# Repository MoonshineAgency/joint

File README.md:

# Joint

Project of the MQTT controller based on the ESP32 for horticulture applications.
Contains firmware and KiCad projects for controllers.

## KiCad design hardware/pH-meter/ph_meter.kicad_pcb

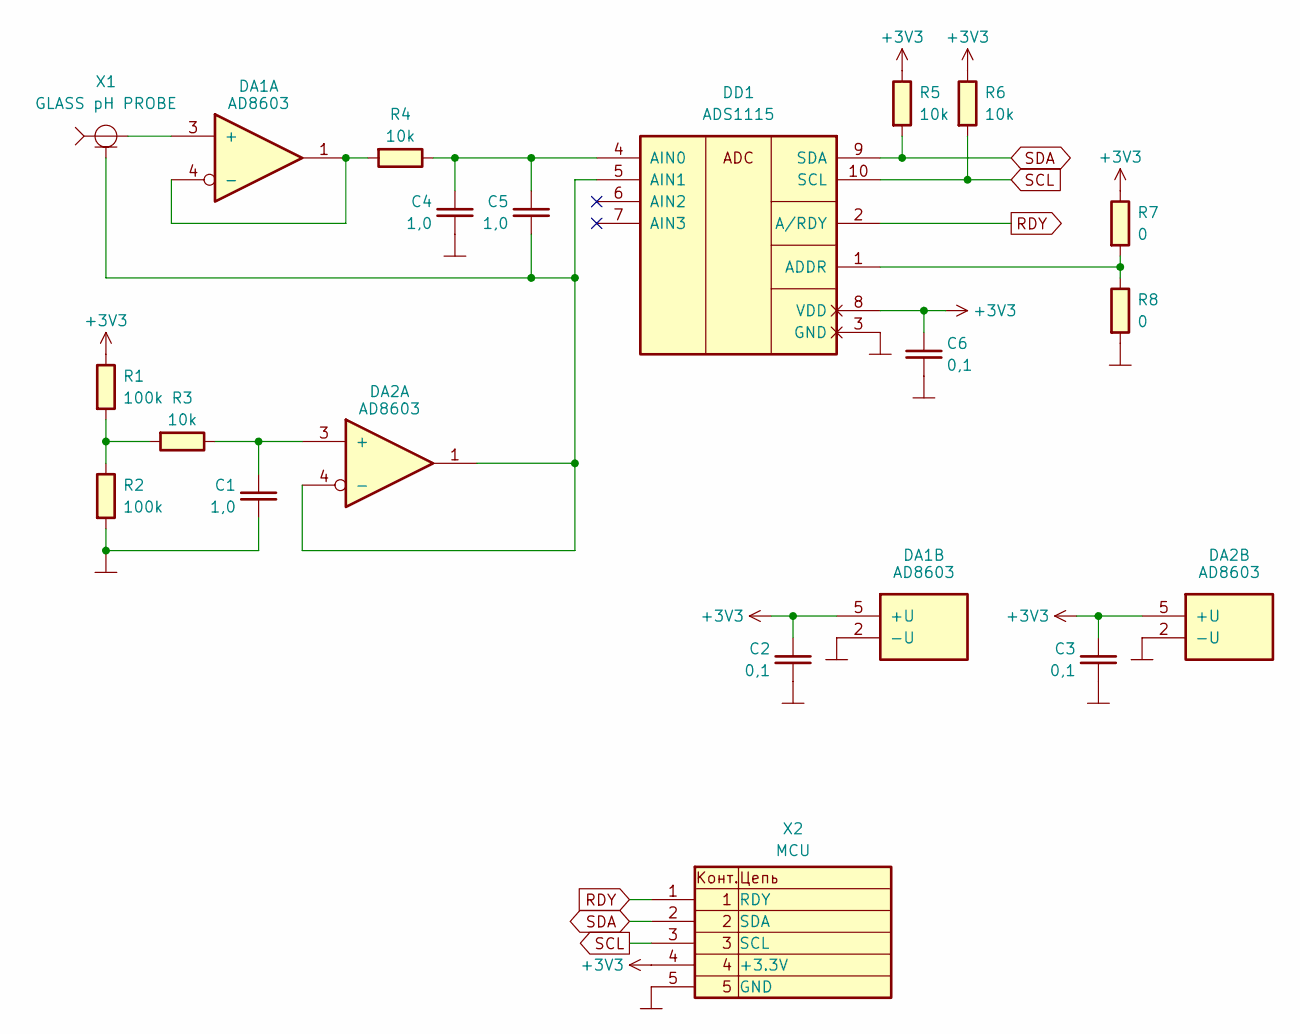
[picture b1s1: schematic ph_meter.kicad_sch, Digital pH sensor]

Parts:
C1, C4, C5: 1,0; C_0805_2012Metric_Pad1.18x1.45mm_HandSolder
C2, C3, C6: 0,1; C_0805_2012Metric_Pad1.18x1.45mm_HandSolder
DA1, DA2: AD8603; TSOT-23-5_HandSoldering
DD1: ADS1115; MSOP-10_3x3mm_P0.5mm
R1, R2: 100k; R_0805_2012Metric_Pad1.20x1.40mm_HandSolder
R3, R4, R5, R6: 10k; R_0805_2012Metric_Pad1.20x1.40mm_HandSolder
R7, R8: 0; R_0805_2012Metric_Pad1.20x1.40mm_HandSolder
X1: GLASS pH PROBE; BNC_Amphenol_B6252HB-NPP3G-50_Horizontal
X2: MCU; PinHeader_1x05_P2.54mm_Vertical

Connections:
+3V3: C2.2, C3.2, C6.2, DA1.5 (+U), DA2.5 (+U), DD1.8 (VDD), R1.2 (R), R5.2 (R), R6.2 (R), R7.2 (R), X2.4
GND: C1.1, C2.1, C3.1, C4.1, C6.1, DA1.2 (-U), DA2.2 (-U), DD1.3 (GND), R2.1 (L), R8.1 (L), X2.5
unnamed: DA1.3 (+), X1.1
unnamed: DA1.1, DA1.4 (-), R4.1 (L)
unnamed: C1.2, DA2.3 (+), R3.2 (R)
unnamed: C5.1, DA2.1, DA2.4 (-), DD1.5 (AIN1), X1.2
unnamed: DD1.1 (ADDR), R7.1 (L), R8.2 (R)
unnamed: C4.2, C5.2, DD1.4 (AIN0), R4.2 (R)
unnamed: R1.1 (L), R2.2 (R), R3.1 (L)
RDY: DD1.2 (A/RDY), X2.1
SCL: DD1.10 (SCL), R6.1 (L), X2.3
SDA: DD1.9 (SDA), R5.1 (L), X2.2

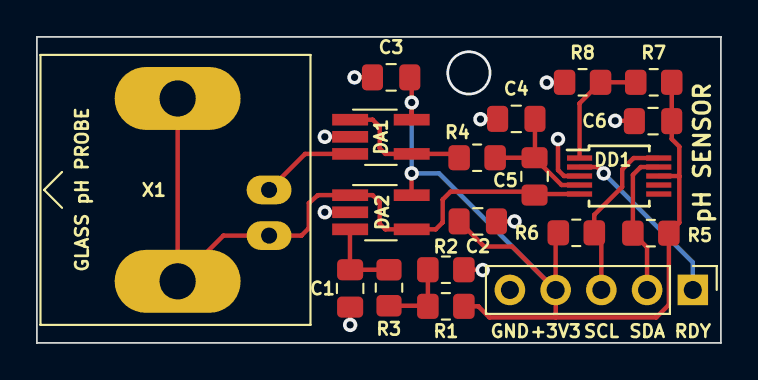
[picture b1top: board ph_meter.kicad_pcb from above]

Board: 2 copper layers, 38.0 x 17.0 mm, 19 parts (0 on the bottom side), 12 nets.

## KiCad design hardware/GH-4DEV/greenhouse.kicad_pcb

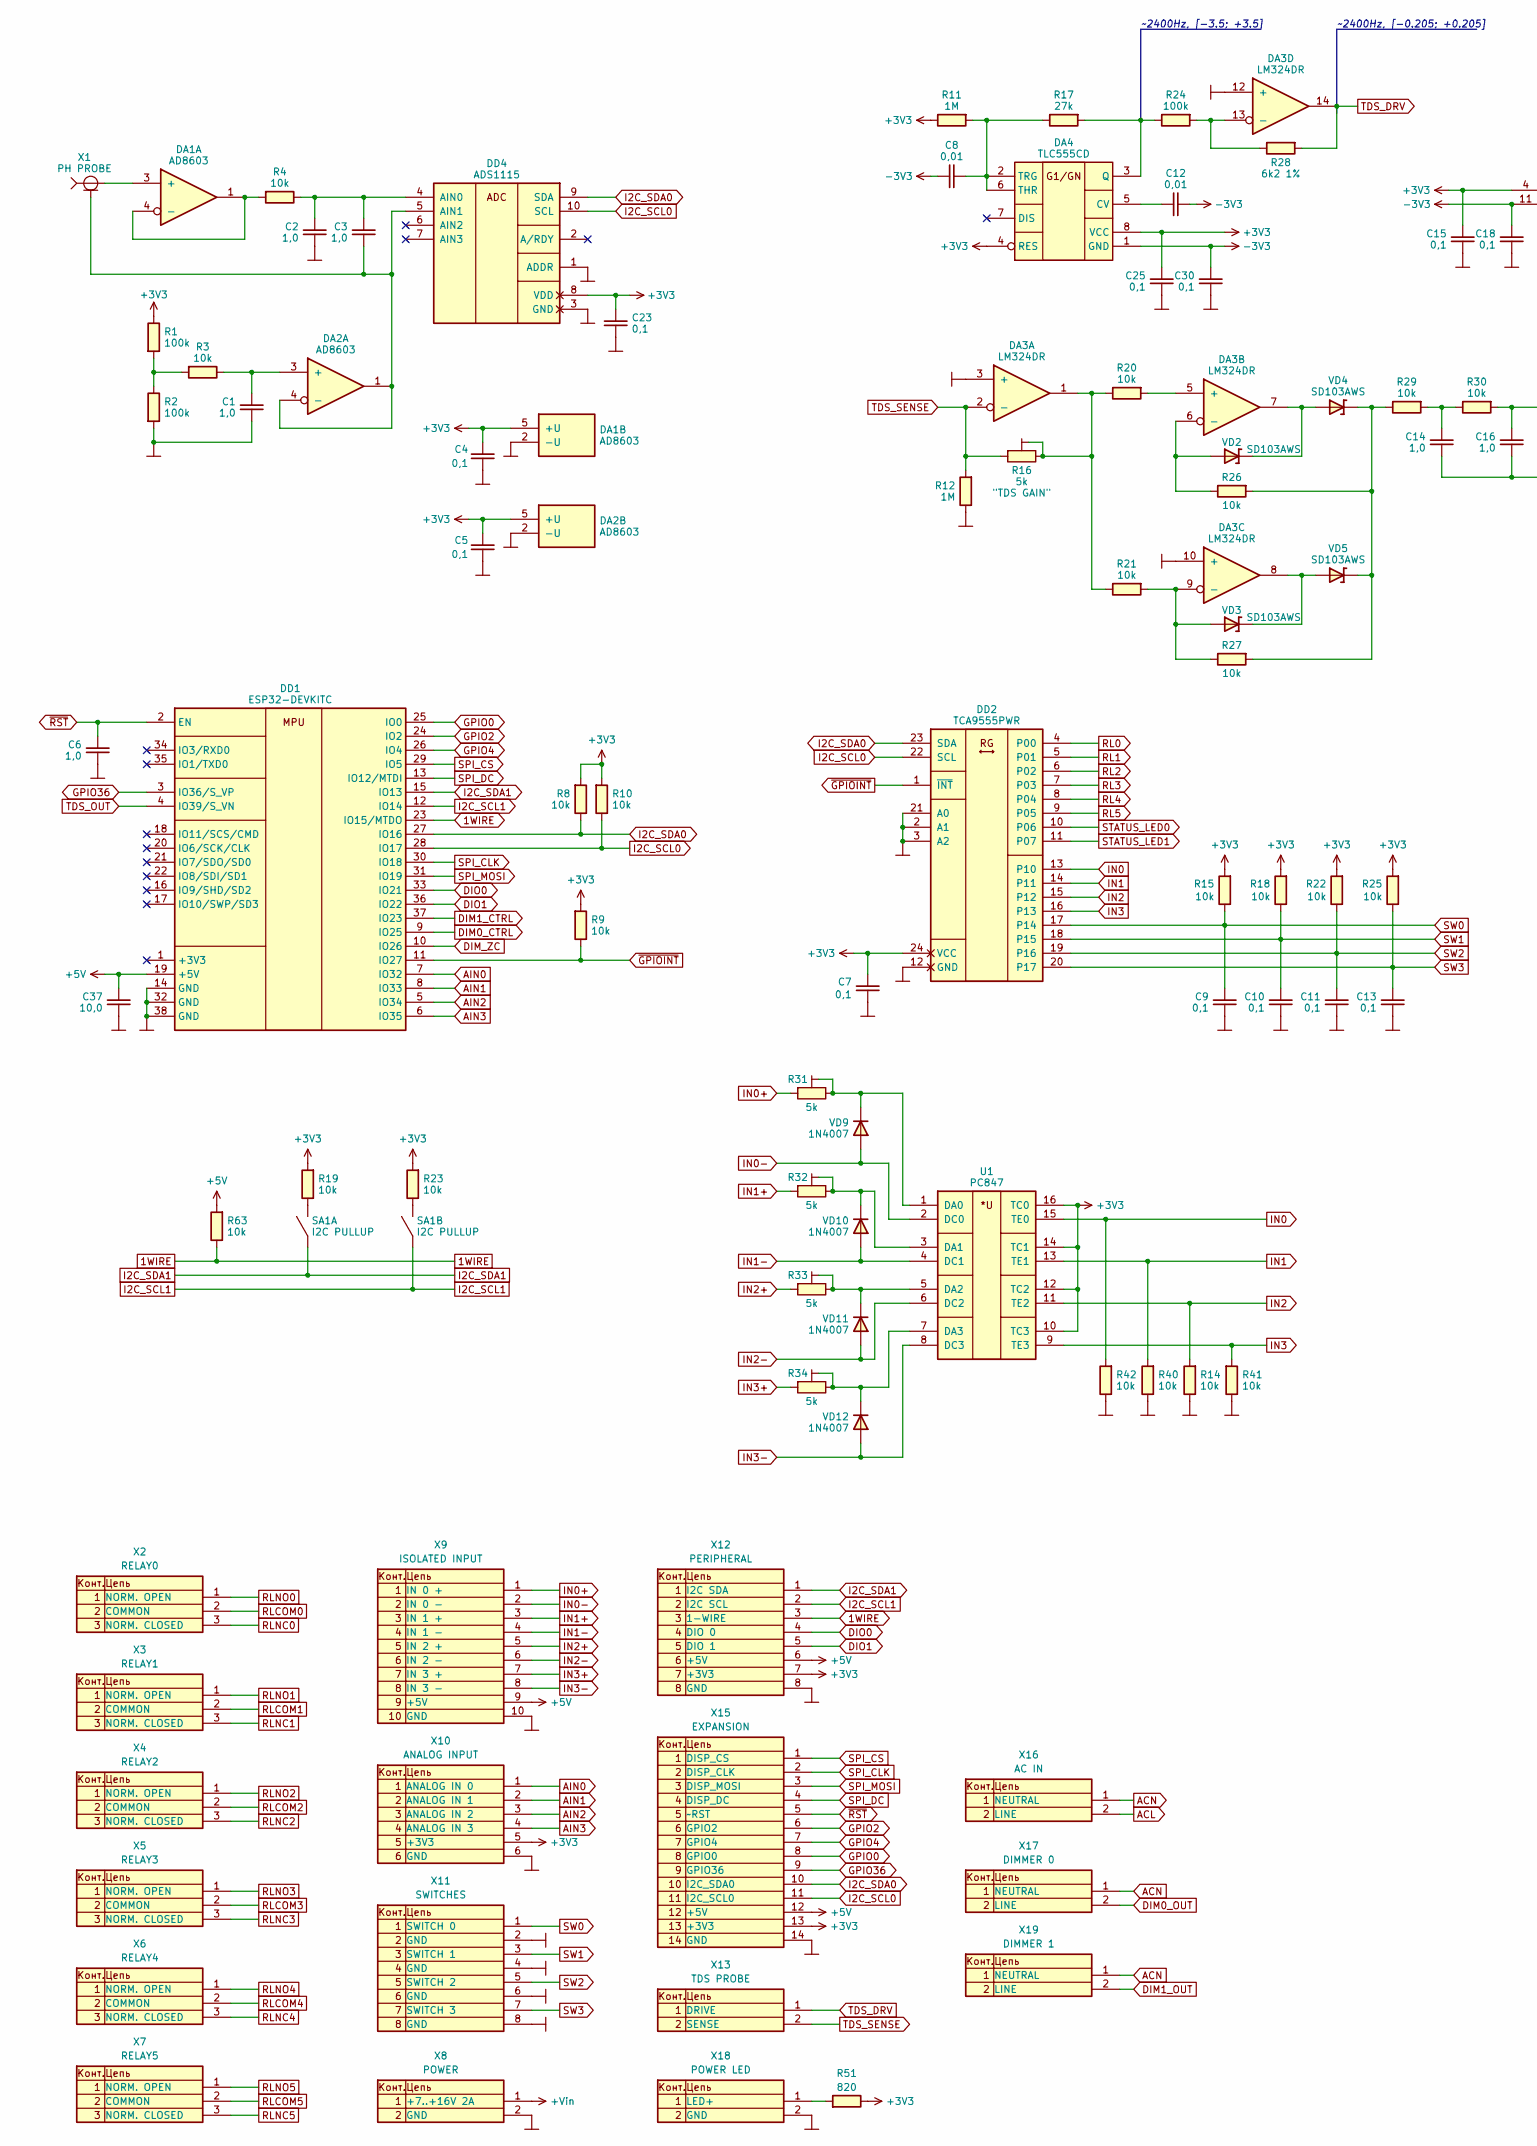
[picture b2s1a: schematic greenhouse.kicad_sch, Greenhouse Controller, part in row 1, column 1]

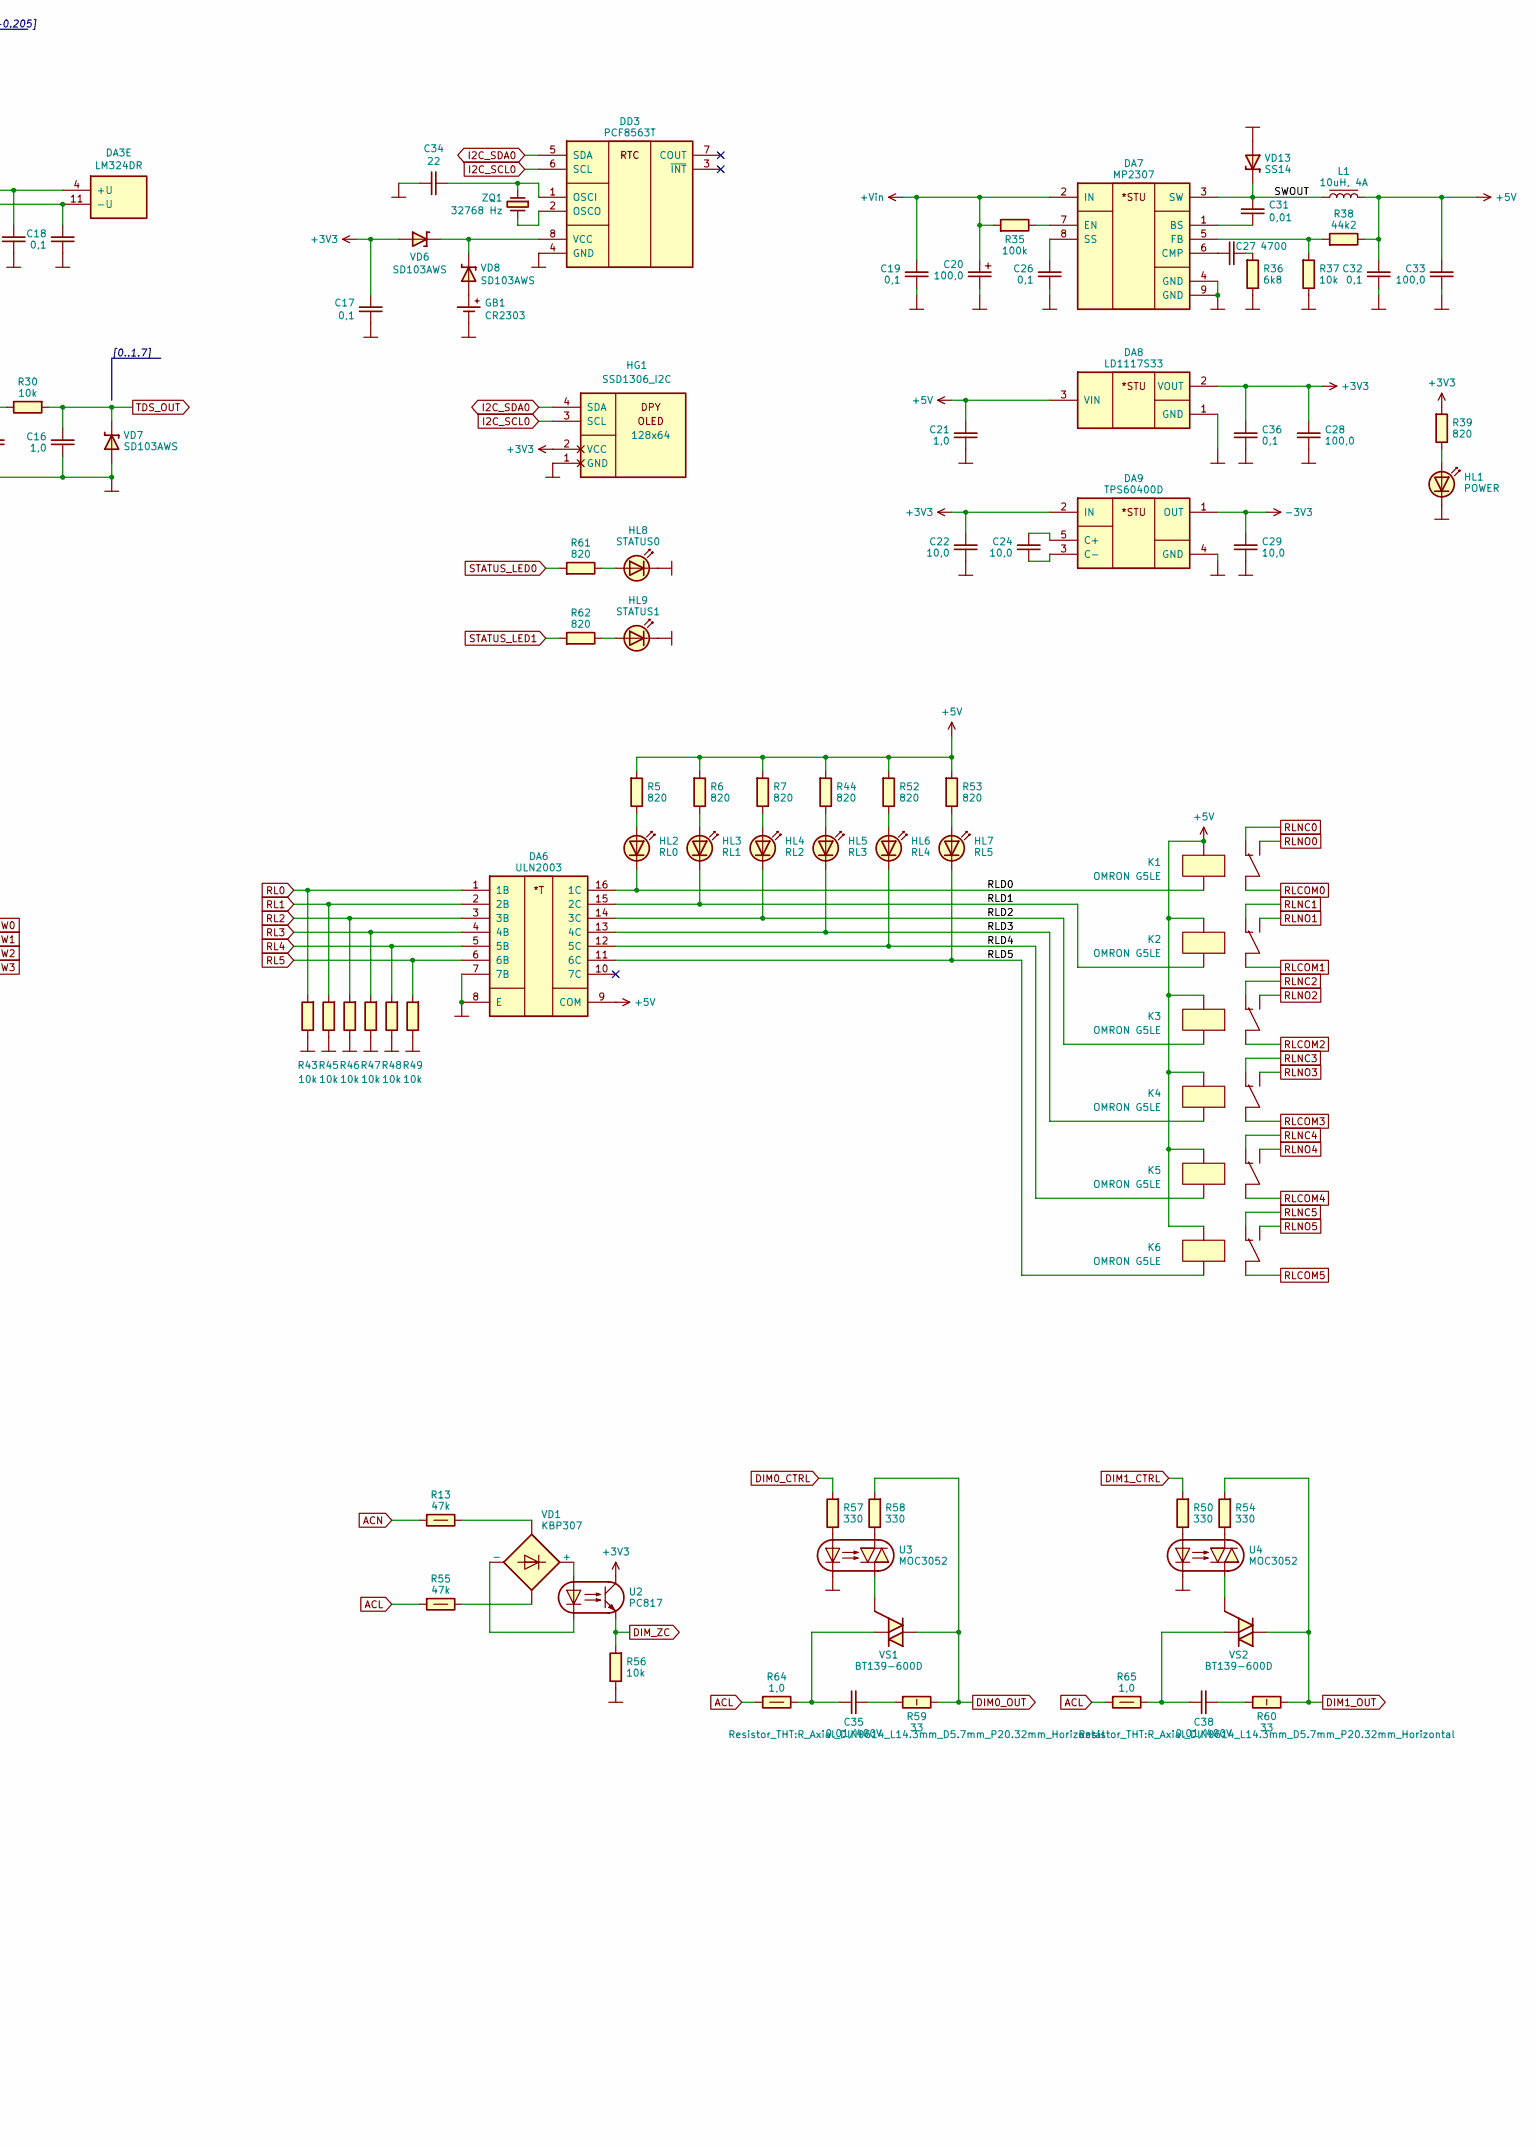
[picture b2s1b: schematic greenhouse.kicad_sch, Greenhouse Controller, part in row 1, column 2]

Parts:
C1, C2, C3, C6, C14, C16, C21: 1,0; C_0805_2012Metric_Pad1.18x1.45mm_HandSolder
C4, C5, C7, C9, C10, C11, C13, C15, C17, C18, C19, C23, C25, C26, C30, C32, C36: 0,1; C_0805_2012Metric_Pad1.18x1.45mm_HandSolder
C8, C12, C31: 0,01; C_0805_2012Metric_Pad1.18x1.45mm_HandSolder
C20: 100,0; CP_EIA-7343-31_Kemet-D_Pad2.25x2.55mm_HandSolder
C22, C24, C29, C37: 10,0; C_0805_2012Metric_Pad1.18x1.45mm_HandSolder
C27: 4700; C_0805_2012Metric_Pad1.18x1.45mm_HandSolder
C28, C33: 100,0; C_1210_3225Metric_Pad1.33x2.70mm_HandSolder
C34: 22; C_0805_2012Metric_Pad1.18x1.45mm_HandSolder
C35, C38: 0,01/400V; C_Rect_L13.0mm_W5.0mm_P10.00mm_FKS3_FKP3_MKS4
DA1, DA2: AD8603; TSOT-23-5_HandSoldering
DA3: LM324DR; SOIC-14_3.9x8.7mm_P1.27mm
DA4: TLC555CD; SOIC-8_3.9x4.9mm_P1.27mm
DA6: ULN2003; SOIC-16_3.9x9.9mm_P1.27mm
DA7: MP2307; HSOP-8-1EP_3.9x4.9mm_P1.27mm_EP2.41x3.1mm_ThermalVias
DA8: LD1117S33; SOT-223-3_TabPin2
DA9: TPS60400D; SOT-23-5_HandSoldering
DD1: ESP32-DEVKITC
DD2: TCA9555PWR; TSSOP-24_4.4x7.8mm_P0.65mm
DD3: PCF8563T; SOIC-8_3.9x4.9mm_P1.27mm
DD4: ADS1115; MSOP-10_3x3mm_P0.5mm
GB1: CR2303; BAT_BS-7
HG1: SSD1306_I2C; SSD1306_0.96_Oled
HL1: POWER; LED_0805_2012Metric_Pad1.15x1.40mm_HandSolder
HL2: RL0; LED_0805_2012Metric_Pad1.15x1.40mm_HandSolder
HL3: RL1; LED_0805_2012Metric_Pad1.15x1.40mm_HandSolder
HL4: RL2; LED_0805_2012Metric_Pad1.15x1.40mm_HandSolder
HL5: RL3; LED_0805_2012Metric_Pad1.15x1.40mm_HandSolder
HL6: RL4; LED_0805_2012Metric_Pad1.15x1.40mm_HandSolder
HL7: RL5; LED_0805_2012Metric_Pad1.15x1.40mm_HandSolder
HL8: STATUS0; LED_0805_2012Metric_Pad1.15x1.40mm_HandSolder
HL9: STATUS1; LED_0805_2012Metric_Pad1.15x1.40mm_HandSolder
K1, K2, K3, K4, K5, K6: OMRON G5LE; Relay_SPDT_Omron-G5LE-1
L1: 10uH, 4A; L_0808
R1, R2, R24, R35: 100k; R_0805_2012Metric_Pad1.20x1.40mm_HandSolder
R3, R4, R8, R9, R10, R14, R15, R18, R19, R20, R21, R22, R23, R25, R26, R27, R29, R30, R37, R40, R41, R42, R43, R45, R46, R47, R48, R49, R56, R63: 10k; R_0805_2012Metric_Pad1.20x1.40mm_HandSolder
R5, R6, R7, R39, R44, R51, R52, R53, R61, R62: 820; R_0805_2012Metric_Pad1.20x1.40mm_HandSolder
R11, R12: 1M; R_0805_2012Metric_Pad1.20x1.40mm_HandSolder
R13, R55: 47k; R_Axial_DIN0309_L9.0mm_D3.2mm_P12.70mm_Horizontal
R16, R31, R32, R33, R34: 5k; Potentiometer_Bourns_3296W_Vertical
R17: 27k; R_0805_2012Metric_Pad1.20x1.40mm_HandSolder
R28: 6k2 1%; R_0805_2012Metric_Pad1.20x1.40mm_HandSolder
R36: 6k8; R_0805_2012Metric_Pad1.20x1.40mm_HandSolder
R38: 44k2; R_0805_2012Metric_Pad1.20x1.40mm_HandSolder
R50, R54, R57, R58: 330; R_0805_2012Metric_Pad1.20x1.40mm_HandSolder
R59, R60: 33; R_Axial_DIN0614_L14.3mm_D5.7mm_P20.32mm_Horizontal
R64, R65: 1,0; R_Axial_DIN0309_L9.0mm_D3.2mm_P2.54mm_Vertical
SA1: I2C PULLUP; SW_DIP_SPSTx02_Slide_6.7x6.64mm_W7.62mm_P2.54mm_LowProfile
U1: PC847; DIP-16_W7.62mm_LongPads
U2: PC817; DIP-4_W7.62mm_LongPads
U3, U4: MOC3052; DIP-6_W7.62mm_LongPads
VD1: KBP307; Diode_Bridge_Vishay_KBPM
VD2, VD3, VD4, VD5, VD6, VD7, VD8: SD103AWS; D_SOD-323_HandSoldering
VD9, VD10, VD11, VD12: 1N4007; D_SOD-123
VD13: SS14; D_SMA
VS1, VS2: BT139-600D; TO-220-3_Vertical
X1: PH PROBE; BNC_Amphenol_B6252HB-NPP3G-50_Horizontal
X2: RELAY0; TerminalBlock_bornier-3_P5.08mm
X3: RELAY1; TerminalBlock_bornier-3_P5.08mm
X4: RELAY2; TerminalBlock_bornier-3_P5.08mm
X5: RELAY3; TerminalBlock_bornier-3_P5.08mm
X6: RELAY4; TerminalBlock_bornier-3_P5.08mm
X7: RELAY5; TerminalBlock_bornier-3_P5.08mm
X8: POWER; TerminalBlock_bornier-2_P5.08mm
X9: ISOLATED INPUT; TerminalBlock_bornier-10_P5.08mm
X10: ANALOG INPUT; TerminalBlock_bornier-6_P5.08mm
X11: SWITCHES; TerminalBlock_bornier-8_P5.08mm
X12: PERIPHERAL; TerminalBlock_bornier-8_P5.08mm
X13: TDS PROBE; TerminalBlock_bornier-2_P5.08mm
X15: EXPANSION; PinHeader_2x07_P2.54mm_Vertical
X16: AC IN; TerminalBlock_bornier-2_P5.08mm
X17: DIMMER 0; TerminalBlock_bornier-2_P5.08mm
X18: POWER LED; PinHeader_1x02_P2.54mm_Vertical
X19: DIMMER 1; TerminalBlock_bornier-2_P5.08mm
ZQ1: 32768 Hz; Crystal_DS26_D2.0mm_L6.0mm_Horizontal

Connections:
1WIRE: DD1.23 (IO15/MTDO), R63.2 (R), X12.3
+3V3: C4.1, C5.1, C7.1, C15.1, C17.1, C22.1, C23.2, C25.1, C28.1, C36.1, DA1.5 (+U), DA2.5 (+U), DA3.4 (+U), DA4.4 (RES), DA4.8 (VCC), DA8.2 (VOUT), DA9.2 (IN), DD2.24 (VCC), DD4.8 (VDD), HG1.2 (VCC), R1.2 (R), R8.1 (L), R9.1 (L), R10.1 (L), R11.2 (R), R15.1 (L), R18.1 (L), R19.1 (L), R22.1 (L), R23.1 (L), R25.1 (L), R39.1 (L), R51.2 (R), U1.10 (TC3), U1.12 (TC2), U1.14 (TC1), U1.16 (TC0), U2.4, VD6.2 (A), X10.5, X12.7, X15.13
+5V: C21.1, C32.1, C33.1, C37.1, DA6.9 (COM), DA8.3 (VIN), DD1.19 (+5V), K1.2, K2.2, K3.2, K4.2, K5.2, K6.2, L1.2, R5.1 (L), R6.1 (L), R7.1 (L), R38.2 (R), R44.1 (L), R52.1 (L), R53.1 (L), R63.1 (L), X9.9, X12.6, X15.12
+Vin: C19.1, C20.1, DA7.2 (IN), R35.1 (L), X8.1
-3V3: C8.2, C12.1, C18.1, C29.1, C30.1, DA3.11 (-U), DA4.1 (GND), DA9.1 (OUT)
/RLD0: DA6.16 (1C), HL2.1 (K), K1.5
/RLD1: DA6.15 (2C), HL3.1 (K), K2.5
/RLD2: DA6.14 (3C), HL4.1 (K), K3.5
/RLD3: DA6.13 (4C), HL5.1 (K), K4.5
/RLD4: DA6.12 (5C), HL6.1 (K), K5.5
/RLD5: DA6.11 (6C), HL7.1 (K), K6.5
/SWOUT: C31.1, DA7.3 (SW), L1.1, VD13.1 (K)
ACL: R55.1 (L), R64.1 (L), R65.1 (L), X16.2
ACN: R13.1 (L), X16.1, X17.1, X19.1
AIN0: DD1.7 (IO32), X10.1
AIN1: DD1.8 (IO33), X10.2
AIN2: DD1.5 (IO34), X10.3
AIN3: DD1.6 (IO35), X10.4
DIM0_CTRL: DD1.9 (IO25), R57.1 (L)
DIM0_OUT: R58.1 (L), R59.2 (R), VS1.2 (A), X17.2
DIM1_CTRL: DD1.37 (IO23), R50.1 (L)
DIM1_OUT: R54.1 (L), R60.2 (R), VS2.2 (A), X19.2
DIM_ZC: DD1.10 (IO26), R56.1 (L), U2.3
DIO0: DD1.33 (IO21), X12.4
DIO1: DD1.36 (IO22), X12.5
GND: C1.1, C2.1, C4.2, C5.2, C6.2, C7.2, C9.2, C10.2, C11.2, C13.2, C14.2, C15.2, C16.2, C17.2, C18.2, C19.2, C20.2, C21.2, C22.2, C23.1, C25.2, C26.2, C28.2, C29.2, C30.2, C32.2, C33.2, C34.2, C36.2, C37.2, DA1.2 (-U), DA2.2 (-U), DA3.3 (+), DA3.10 (+), DA3.12 (+), DA6.7 (7B), DA6.8 (E), DA7.4 (GND), DA7.9 (GND), DA8.1 (GND), DA9.4 (GND), DD1.14 (GND), DD1.32 (GND), DD1.38 (GND), DD2.2 (A1), DD2.3 (A2), DD2.12 (GND), DD2.21 (A0), DD3.4 (GND), DD4.1 (ADDR), DD4.3 (GND), GB1.2, HG1.1 (GND), HL1.1 (K), HL8.1 (K), HL9.1 (K), R2.1 (L), R12.2 (R), R14.2 (R), R36.2 (R), R37.2 (R), R40.2 (R), R41.2 (R), R42.2 (R), R43.2 (R), R45.2 (R), R46.2 (R), R47.2 (R), R48.2 (R), R49.2 (R), R56.2 (R), U3.2, U4.2, VD7.2 (A), VD13.2 (A), X8.2, X9.10, X10.6, X11.2, X11.4, X11.6, X11.8, X12.8, X15.14, X18.2
GPIO0: DD1.25 (IO0), X15.8
GPIO2: DD1.24 (IO2), X15.6
GPIO4: DD1.26 (IO4), X15.7
GPIO36: DD1.3 (IO36/S_VP), X15.9
I2C_SCL0: DD1.28 (IO17), DD2.22 (SCL), DD3.6 (SCL), DD4.10 (SCL), HG1.3 (SCL), R10.2 (R), X15.11
I2C_SCL1: DD1.12 (IO14), SA1.2 (L), X12.2
I2C_SDA0: DD1.27 (IO16), DD2.23 (SDA), DD3.5 (SDA), DD4.9 (SDA), HG1.4 (SDA), R8.2 (R), X15.10
I2C_SDA1: DD1.15 (IO13), SA1.1 (L), X12.1
IN0: DD2.13 (P10), R42.1 (L), U1.15 (TE0)
IN0+: R31.1, X9.1
IN0-: U1.2 (DC0), VD9.2 (A), X9.2
IN1: DD2.14 (P11), R40.1 (L), U1.13 (TE1)
IN1+: R32.1, X9.3
IN1-: U1.4 (DC1), VD10.2 (A), X9.4
IN2: DD2.15 (P12), R14.1 (L), U1.11 (TE2)
IN2+: R33.1, X9.5
IN2-: U1.6 (DC2), VD11.2 (A), X9.6
IN3: DD2.16 (P13), R41.1 (L), U1.9 (TE3)
IN3+: R34.1, X9.7
IN3-: U1.8 (DC3), VD12.2 (A), X9.8
unnamed: DA1.3 (+), X1.1
unnamed: DA1.1, DA1.4 (-), R4.1 (L)
unnamed: C1.2, DA2.3 (+), R3.2 (R)
unnamed: C3.1, DA2.1, DA2.4 (-), DD4.5 (AIN1), X1.2
unnamed: DA3.5 (+), R20.1 (L)
unnamed: DA3.6 (-), R26.2 (R), VD2.2 (A)
unnamed: DA3.9 (-), R21.1 (L), R27.2 (R), VD3.2 (A)
unnamed: DA3.13 (-), R24.1 (L), R28.2 (R)
unnamed: C12.2, DA4.5 (CV)
unnamed: DA4.3 (Q), R17.1 (L), R24.2 (R)
unnamed: C8.1, DA4.2 (TRG), DA4.6 (THR), R11.1 (L), R17.2 (R)
unnamed: C31.2, DA7.1 (BS)
unnamed: C27.2, DA7.6 (CMP)
unnamed: DA7.7 (EN), R35.2 (R)
unnamed: DA7.5 (FB), R37.1 (L), R38.1 (L)
unnamed: C26.1, DA7.8 (SS)
unnamed: C24.1, DA9.5 (C+)
unnamed: C24.2, DA9.3 (C-)
unnamed: C34.1, DD3.1 (OSCI), ZQ1.1
unnamed: DD3.2 (OSCO), ZQ1.2
unnamed: DD3.8 (VCC), VD6.1 (K), VD8.1 (K)
unnamed: C2.2, C3.2, DD4.4 (AIN0), R4.2 (R)
unnamed: HL1.2 (A), R39.2 (R)
unnamed: HL2.2 (A), R5.2 (R)
unnamed: HL3.2 (A), R6.2 (R)
unnamed: HL4.2 (A), R7.2 (R)
unnamed: HL5.2 (A), R44.2 (R)
unnamed: HL6.2 (A), R52.2 (R)
unnamed: HL7.2 (A), R53.2 (R)
unnamed: HL8.2 (A), R61.2 (R)
unnamed: HL9.2 (A), R62.2 (R)
unnamed: R1.1 (L), R2.2 (R), R3.1 (L)
unnamed: R13.2 (R), VD1.2
unnamed: R19.2 (R), SA1.4 (R)
unnamed: DA3.1, R16.2, R16.3, R20.2 (R), R21.2 (R)
unnamed: R23.2 (R), SA1.3 (R)
unnamed: R26.1 (L), R27.1 (L), R29.2 (R), VD4.1 (K), VD5.1 (K)
unnamed: C14.1, R29.1 (L), R30.2 (R)
unnamed: C27.1, R36.1 (L)
unnamed: R50.2 (R), U4.1
unnamed: R51.1 (L), X18.1
unnamed: R54.2 (R), U4.6
unnamed: R55.2 (R), VD1.3
unnamed: R57.2 (R), U3.1
unnamed: R58.2 (R), U3.6
unnamed: C35.2, R59.1 (L)
unnamed: C38.2, R60.1 (L)
unnamed: C35.1, R64.2 (R), VS1.1 (K)
unnamed: C38.1, R65.2 (R), VS2.1 (K)
unnamed: R31.2, R31.3, U1.1 (DA0), VD9.1 (K)
unnamed: R32.2, R32.3, U1.3 (DA1), VD10.1 (K)
unnamed: R33.2, R33.3, U1.5 (DA2), VD11.1 (K)
unnamed: R34.2, R34.3, U1.7 (DA3), VD12.1 (K)
unnamed: U2.1, VD1.1 (+)
unnamed: U2.2, VD1.4 (-)
unnamed: DA3.7, VD2.1 (K), VD4.2 (A)
unnamed: DA3.8, VD3.1 (K), VD5.2 (A)
unnamed: GB1.1, VD8.2 (A)
unnamed: U3.4, VS1.3 (G)
unnamed: U4.4, VS2.3 (G)
RL0: DA6.1 (1B), DD2.4 (P00), R43.1 (L)
RL1: DA6.2 (2B), DD2.5 (P01), R45.1 (L)
RL2: DA6.3 (3B), DD2.6 (P02), R46.1 (L)
RL3: DA6.4 (4B), DD2.7 (P03), R47.1 (L)
RL4: DA6.5 (5B), DD2.8 (P04), R48.1 (L)
RL5: DA6.6 (6B), DD2.9 (P05), R49.1 (L)
RLCOM0: K1.1, X2.2
RLCOM1: K2.1, X3.2
RLCOM2: K3.1, X4.2
RLCOM3: K4.1, X5.2
RLCOM4: K5.1, X6.2
RLCOM5: K6.1, X7.2
RLNC0: K1.4, X2.3
RLNC1: K2.4, X3.3
RLNC2: K3.4, X4.3
RLNC3: K4.4, X5.3
RLNC4: K5.4, X6.3
RLNC5: K6.4, X7.3
RLNO0: K1.3, X2.1
RLNO1: K2.3, X3.1
RLNO2: K3.3, X4.1
RLNO3: K4.3, X5.1
RLNO4: K5.3, X6.1
RLNO5: K6.3, X7.1
SPI_CLK: DD1.30 (IO18), X15.2
SPI_CS: DD1.29 (IO5), X15.1
SPI_DC: DD1.13 (IO12/MTDI), X15.4
SPI_MOSI: DD1.31 (IO19), X15.3
STATUS_LED0: DD2.10 (P06), R61.1 (L)
STATUS_LED1: DD2.11 (P07), R62.1 (L)
SW0: C9.1, DD2.17 (P14), R15.2 (R), X11.1
SW1: C10.1, DD2.18 (P15), R18.2 (R), X11.3
SW2: C11.1, DD2.19 (P16), R22.2 (R), X11.5
SW3: C13.1, DD2.20 (P17), R25.2 (R), X11.7
TDS_DRV: DA3.14, R28.1 (L), X13.1
TDS_OUT: C16.1, DD1.4 (IO39/S_VN), R30.1 (L), VD7.1 (K)
TDS_SENSE: DA3.2 (-), R12.1 (L), R16.1, X13.2
~GPIOINT: DD1.11 (IO27), DD2.1 (~INT), R9.2 (R)
~RST: C6.1, DD1.2 (EN), X15.5

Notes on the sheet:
~2400Hz, [-3.5; +3.5]
~2400Hz, [-0.205; +0.205]
[0..1.7]

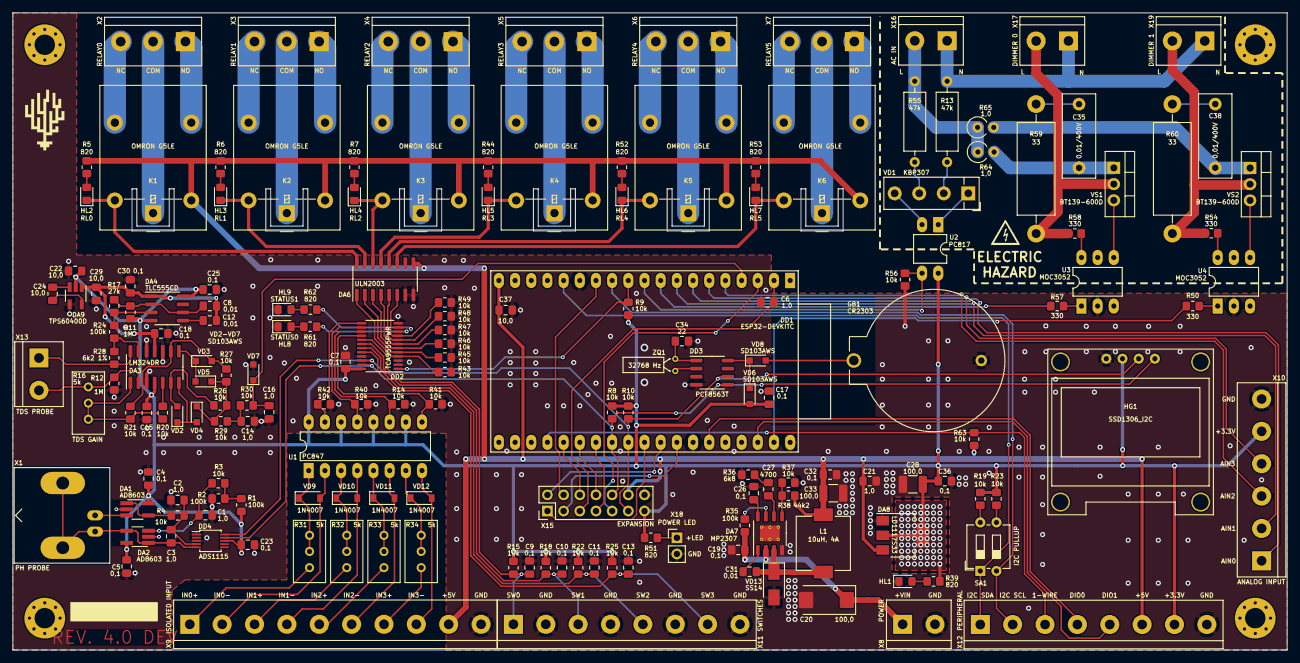
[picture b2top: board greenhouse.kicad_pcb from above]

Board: 2 copper layers, 200.0 x 100.0 mm, 176 parts (0 on the bottom side), 145 nets.

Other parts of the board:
XS1, XS2, XS3, XS4: M3 3.2mm; MountingHole_3.2mm_M3_Pad_Via

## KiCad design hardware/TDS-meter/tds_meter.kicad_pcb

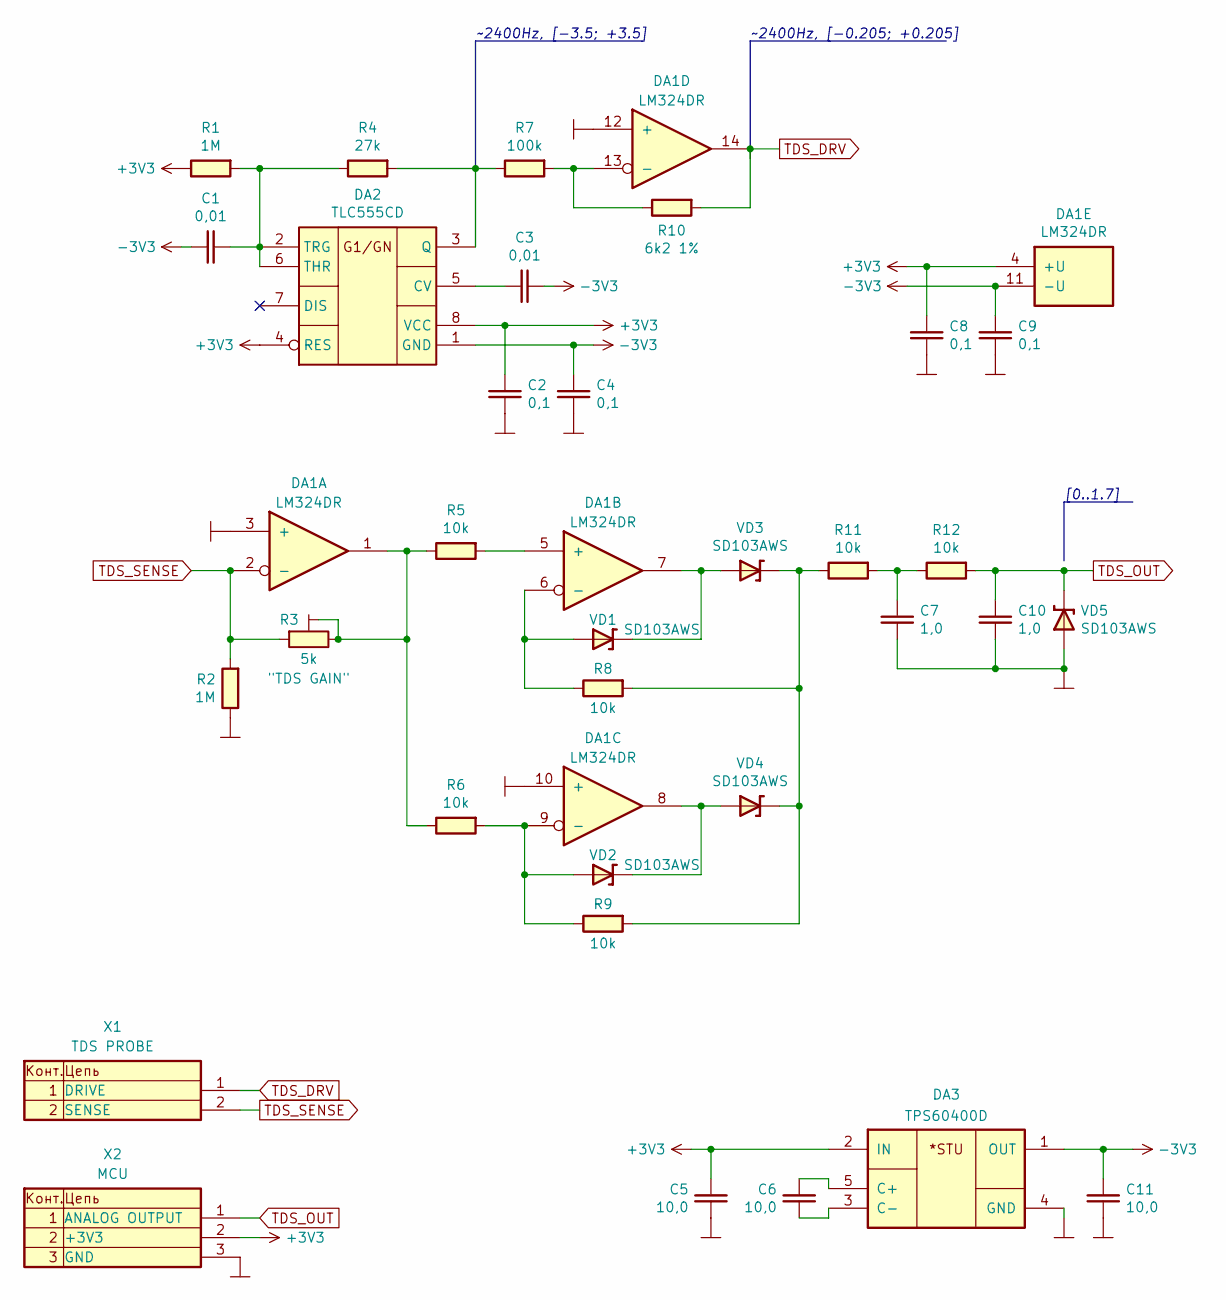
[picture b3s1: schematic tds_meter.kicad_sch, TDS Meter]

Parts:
C1, C3: 0,01; C_0805_2012Metric_Pad1.18x1.45mm_HandSolder
C2, C4, C8, C9: 0,1; C_0805_2012Metric_Pad1.18x1.45mm_HandSolder
C5, C6, C11: 10,0; C_0805_2012Metric_Pad1.18x1.45mm_HandSolder
C7, C10: 1,0; C_0805_2012Metric_Pad1.18x1.45mm_HandSolder
DA1: LM324DR; SOIC-14_3.9x8.7mm_P1.27mm
DA2: TLC555CD; SOIC-8_3.9x4.9mm_P1.27mm
DA3: TPS60400D; SOT-23-5_HandSoldering
R1, R2: 1M; R_0805_2012Metric_Pad1.20x1.40mm_HandSolder
R3: 5k; Potentiometer_Bourns_3296W_Vertical
R4: 27k; R_0805_2012Metric_Pad1.20x1.40mm_HandSolder
R5, R6, R8, R9, R11, R12: 10k; R_0805_2012Metric_Pad1.20x1.40mm_HandSolder
R7: 100k; R_0805_2012Metric_Pad1.20x1.40mm_HandSolder
R10: 6k2 1%; R_0805_2012Metric_Pad1.20x1.40mm_HandSolder
VD1, VD2, VD3, VD4, VD5: SD103AWS; D_SOD-323_HandSoldering
X1: TDS PROBE; TerminalBlock_bornier-2_P5.08mm
X2: MCU; PinHeader_1x03_P2.54mm_Vertical

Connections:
+3V3: C2.1, C5.1, C8.1, DA1.4 (+U), DA2.4 (RES), DA2.8 (VCC), DA3.2 (IN), R1.2 (R), X2.2
-3V3: C1.2, C3.1, C4.1, C9.1, C11.1, DA1.11 (-U), DA2.1 (GND), DA3.1 (OUT)
GND: C2.2, C4.2, C5.2, C7.2, C8.2, C9.2, C10.2, C11.2, DA1.3 (+), DA1.10 (+), DA1.12 (+), DA3.4 (GND), R2.2 (R), VD5.2 (A), X2.3
unnamed: DA1.5 (+), R5.1 (L)
unnamed: DA1.6 (-), R8.2 (R), VD1.2 (A)
unnamed: DA1.9 (-), R6.1 (L), R9.2 (R), VD2.2 (A)
unnamed: DA1.13 (-), R7.1 (L), R10.2 (R)
unnamed: C3.2, DA2.5 (CV)
unnamed: DA2.3 (Q), R4.1 (L), R7.2 (R)
unnamed: C1.1, DA2.2 (TRG), DA2.6 (THR), R1.1 (L), R4.2 (R)
unnamed: C6.1, DA3.5 (C+)
unnamed: C6.2, DA3.3 (C-)
unnamed: DA1.1, R3.2, R3.3, R5.2 (R), R6.2 (R)
unnamed: C7.1, R11.1 (L), R12.2 (R)
unnamed: R8.1 (L), R9.1 (L), R11.2 (R), VD3.1 (K), VD4.1 (K)
unnamed: DA1.7, VD1.1 (K), VD3.2 (A)
unnamed: DA1.8, VD2.1 (K), VD4.2 (A)
TDS_DRV: DA1.14, R10.1 (L), X1.1
TDS_OUT: C10.1, R12.1 (L), VD5.1 (K), X2.1
TDS_SENSE: DA1.2 (-), R2.1 (L), R3.1, X1.2

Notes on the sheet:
~2400Hz, [-3.5; +3.5]
~2400Hz, [-0.205; +0.205]
[0..1.7]

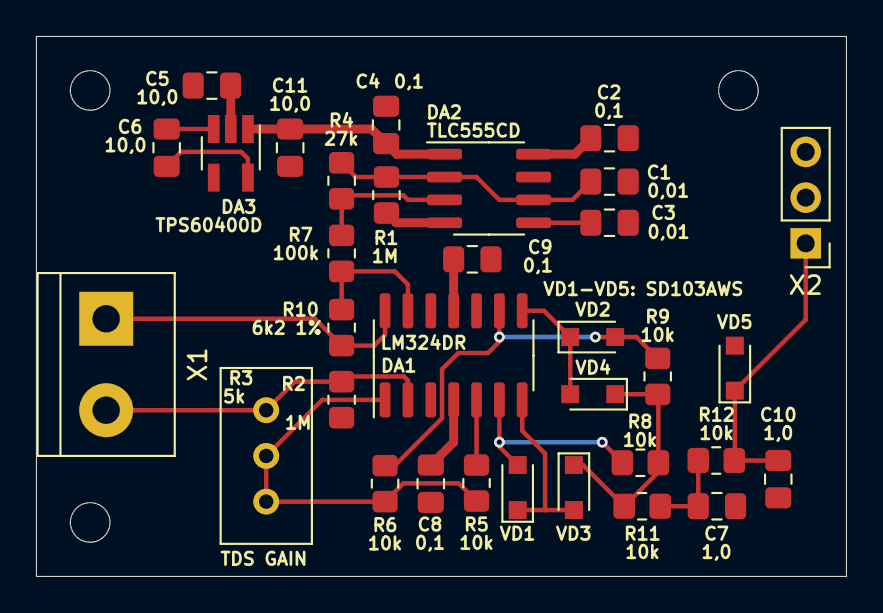
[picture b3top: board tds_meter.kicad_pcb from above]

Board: 2 copper layers, 45.0 x 30.0 mm, 33 parts (0 on the bottom side), 20 nets.

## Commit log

2022-01-03 application skel
2022-01-03 fix warnings
2022-01-12 App skel
2022-06-23 moved to c++, add driver concept, first working proto
2022-06-23 fix drivers initialization in node, add const parameters to Kconfig
2022-06-28 back to C
2022-06-29 GH IO driver, GH ADC driver
2022-06-30 small fixes
2022-07-04 GH IO PH driver, RTC, SNMP client
2022-07-04 update esp-idf-lib
2022-07-04 fix topics for aht and ds18x20
2022-07-04 add clang-format, update esp-idf-lib
2022-07-10 driver config, fix wifi settings bug etc
2022-07-18 add devices; add mqtt discovery
2022-07-18 rename drivers
2022-07-19 add driver config by mqtt msg, fix cvector realloc error
2022-07-19 fix mqtt resub, fix moisture sensor calc, fix mem leak in node
2022-07-22 fix DEV_NUMBER, add device info to mqtt discovery
2022-07-29 fix defconfig in drivers, add dht driver
2022-08-02 add "expire_after" to sensors, add mqtt client state
2022-08-08 update to latest esp-idf-lib, fix printf() format
2022-11-19 update to latest esp-idf and esp-idf-lib
2022-12-07 code cleanup
2022-12-09 refactor drv_gh_adc
2023-03-06 add simpler api, fix UTC+/-, fix drivers
2023-03-13 (feat) add target boards, optimize drivers, driver configs
2023-03-13 (fix) remove unused files
2023-03-14 (feat) script to fast update board settings to dev
2023-06-09 feat: add dimmer driver, add GH-4DEV support, refactor hw_rtc
2023-06-10 add ds3231 rtc, fix dimmer
2023-06-10 add boards schematics and pcb
2023-06-10 fix: update esp-idf-lib
2023-06-10 add basic readme
2023-06-12 fix: update hw to kicad 7, fix capacitor placement in 4.0dev
2023-06-12 feat: add hw for tds & ph meters
2023-06-20 Мелкие правки в железе и диммере
2023-06-26 fix bug in hwrtc, remove dimmer, update esp-idf-lib
2023-06-26 add multisampling to aht
2023-06-26 allow drivers without config
2023-07-02 fix boards/drivers conditional build
2023-10-27 move sntp from config to settings, fix settings errors
2023-12-02 fix system time, update gh_io for gh4 board
2023-12-02 add calibration support to gh_ph_meter, gh_adc, fix settings
2023-12-05 fix post states of devices bug
2023-12-05 fix name of moisture sensors
2023-12-05 add driver configs description, fix show wifi passwd in console
2023-12-08 add support for si7021-compatible sensors, fix adc tds voltage bug, update settings
2023-12-15 add v4.2 board, add option to disable tds in gh_adc driver
2023-12-16 unify calibration json, remove unused code
2023-12-17 move topic definitions to config.h
2023-12-17 add max driver config length as config option
2023-12-17 move std_strings.h to main tree
2024-02-11 update system clock, multiple fixes
